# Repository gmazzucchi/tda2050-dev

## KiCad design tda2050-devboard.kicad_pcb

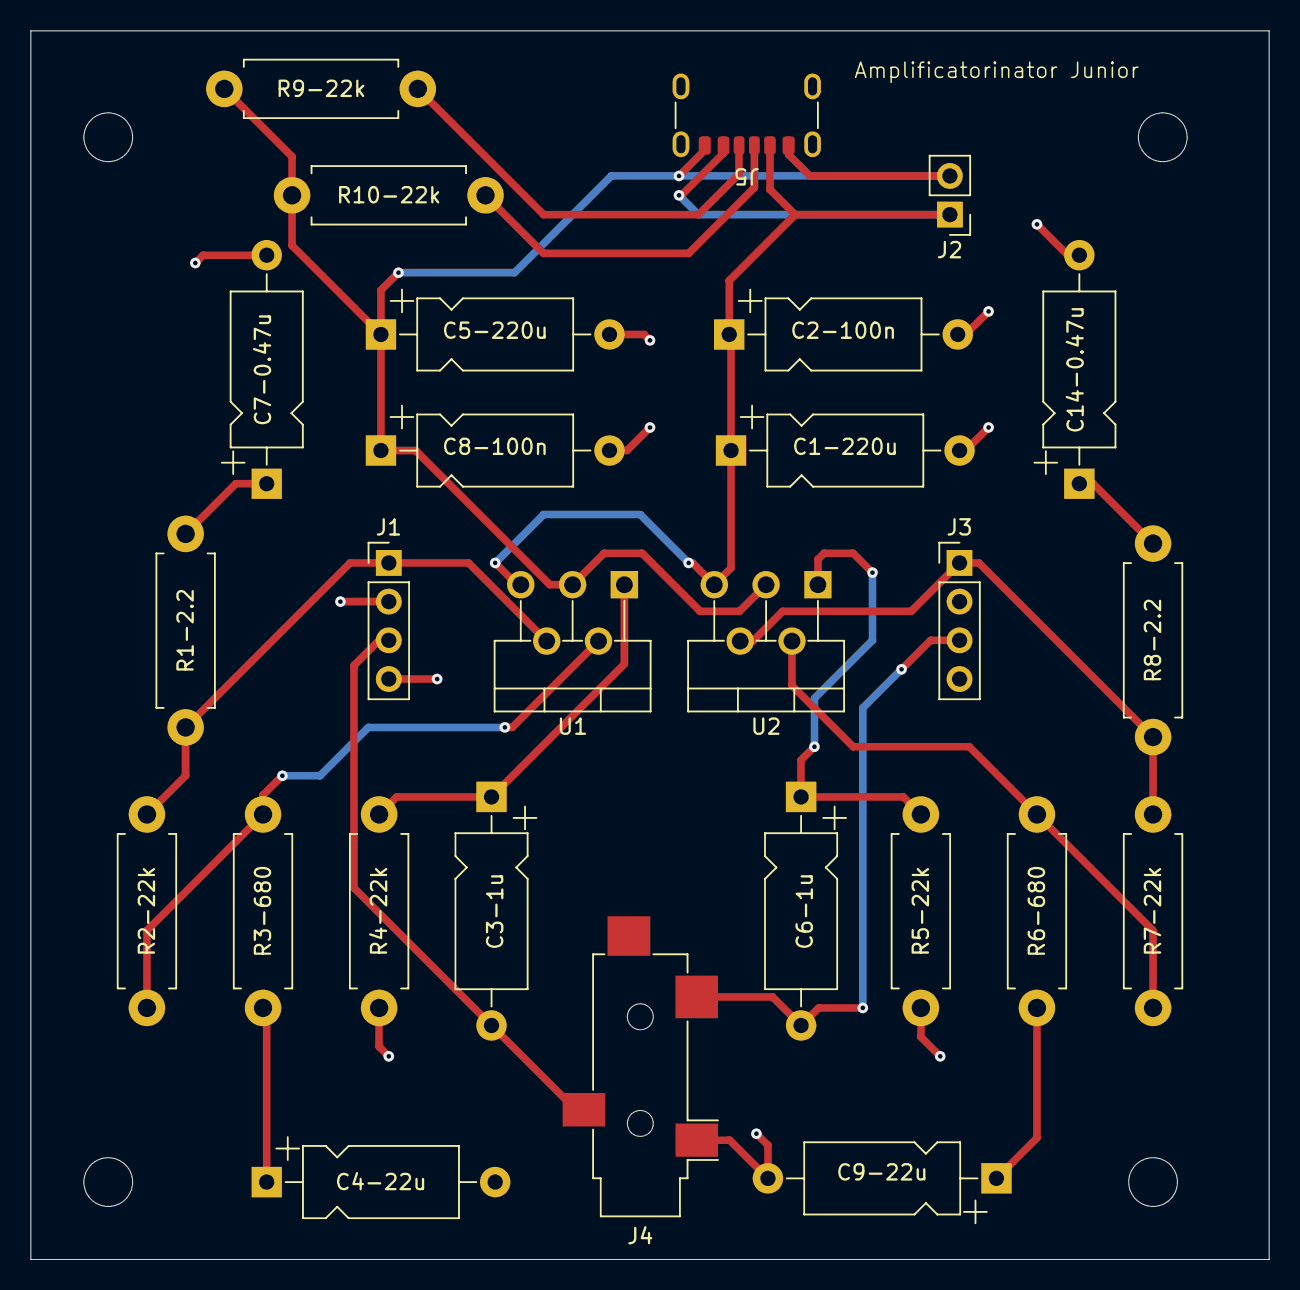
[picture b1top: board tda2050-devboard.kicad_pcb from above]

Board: 2 copper layers, 81.3 x 80.6 mm, 31 parts (0 on the bottom side), 17 nets.

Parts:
C1-220u, C5-220u: 220u; CP_Axial_L10.0mm_D4.5mm_P15.00mm_Horizontal
C2-100n, C8-100n: 100n; CP_Axial_L10.0mm_D4.5mm_P15.00mm_Horizontal
C3-1u, C6-1u: 1u; CP_Axial_L10.0mm_D4.5mm_P15.00mm_Horizontal
C4-22u, C9-22u: 22u; CP_Axial_L10.0mm_D4.5mm_P15.00mm_Horizontal
C7-0.47u, C14-0.47u: 0.47u; CP_Axial_L10.0mm_D4.5mm_P15.00mm_Horizontal
H1, H2, H3, H4: MountingHole; MountingHole_3.2mm_M3
J1, J3: Conn_01x04; PinHeader_1x04_P2.54mm_Vertical
J2: Conn_01x02; PinHeader_1x02_P2.54mm_Vertical
J4: AudioJack3; Jack_3.5mm_CUI_SJ-3524-SMT_Horizontal
J5: USB_C_Receptacle_PowerOnly_6P; USB_C_Receptacle_GCT_USB4125-xx-x_6P_TopMnt_Horizontal
R1-2.2, R8-2.2: 2.2; R_Axial_DIN0411_L9.9mm_D3.6mm_P12.70mm_Horizontal
R2-22k, R4-22k, R5-22k, R7-22k, R9-22k, R10-22k: 22k; R_Axial_DIN0411_L9.9mm_D3.6mm_P12.70mm_Horizontal
R3-680, R6-680: 680; R_Axial_DIN0411_L9.9mm_D3.6mm_P12.70mm_Horizontal
U1, U2: TDA2050; TO-220-5_P3.4x3.7mm_StaggerOdd_Lead3.8mm_Vertical

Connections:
/IN_LEFT: C6-1u.2, J3.3, J4.T
/IN_RIGHT: C3-1u.2, J1.3, J4.R
/SPEAKER_LEFT+: J3.1, R7-22k.2, R8-2.2.1, U2.4
/SPEAKER_RIGHT+: J1.1, R1-2.2.1, R2-22k.2, U1.4
/VS+: C1-220u.1, C2-100n.1, J2.1, J5.A9 (VBUS), J5.B9 (VBUS), U1.5 (+Vs), U2.5 (+Vs)
/VS-: C5-220u.1, C8-100n.1, J2.2, J5.A12 (GND), J5.B12 (GND), R9-22k.2, R10-22k.2, U1.3 (-Vs), U2.3 (-Vs)
GND: C1-220u.2, C2-100n.2, C4-22u.2, C5-220u.2, C7-0.47u.2, C8-100n.2, C9-22u.2, C14-0.47u.2, J1.2, J1.4, J3.2, J3.4, J4.S, R4-22k.2, R5-22k.2
unnamed: C4-22u.1, R3-680.2
unnamed: C7-0.47u.1, R1-2.2.2
unnamed: C9-22u.1, R6-680.2
unnamed: C14-0.47u.1, R8-2.2.2
unnamed: J5.A5 (CC1), R10-22k.1
unnamed: J5.B5 (CC2), R9-22k.1
unnamed: C3-1u.1, R4-22k.1, U1.1 (+)
unnamed: R2-22k.1, R3-680.1, U1.2 (-)
unnamed: C6-1u.1, R5-22k.1, U2.1 (+)
unnamed: R6-680.1, R7-22k.1, U2.2 (-)

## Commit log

2024-04-27 to production
